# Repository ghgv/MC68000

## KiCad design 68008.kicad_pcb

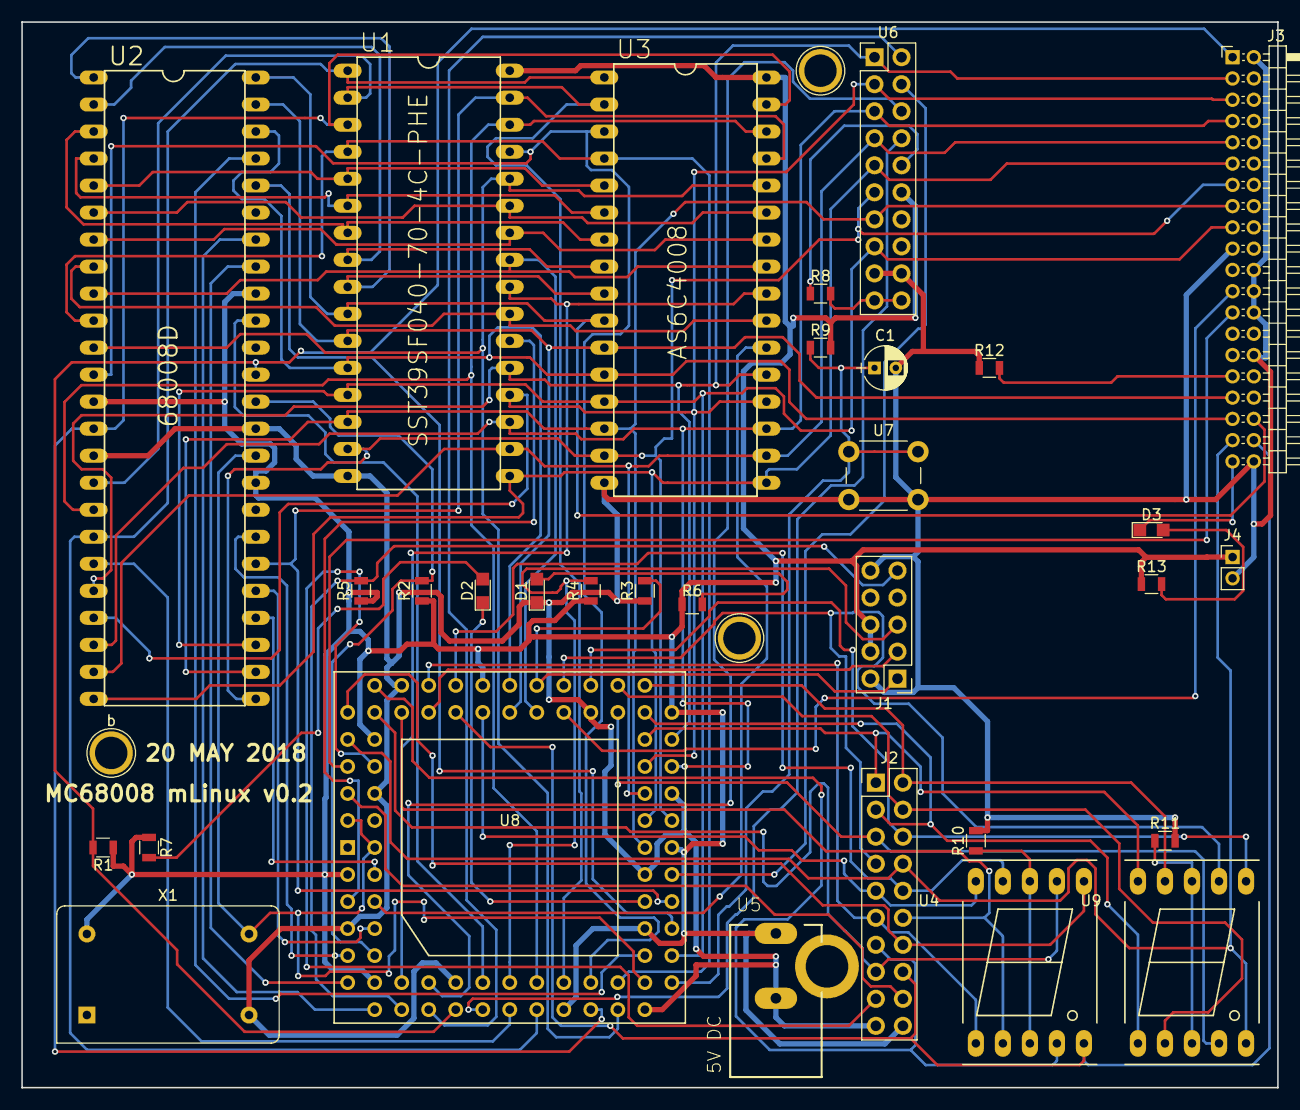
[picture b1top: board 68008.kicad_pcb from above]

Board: 2 copper layers, 118.1 x 100.2 mm, 34 parts (0 on the bottom side), 84 nets.

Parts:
C1: 10uF; CP_Radial_D4.0mm_P2.00mm
D1: Power; LED_0805
D2: status; LED_0805
D3: IDE; LED_0805
J1: CPLD; Pin_Header_Straight_2x05_Pitch2.54mm
J2: PORTS; Pin_Header_Straight_2x10_Pitch2.54mm
J3: Conn_02x20_Odd_Even; Pin_Header_Angled_2x20_Pitch2.00mm
J4: Conn_01x02; Pin_Header_Straight_1x02_Pitch2.00mm
R1, R2, R3, R4, R5: 10K; R_0805
R6, R7, R12, R13: 1K; R_0805
R8: 10KR; R_0805
R9: R; R_0805
R10, R11: 680; R_0805
U1: SST39SF040-70-4C-PHE; DIL32
U2: 68008D; DIL48
U3: AS6C4008; DIL32
U4: Hi; 7SegmentLED_LTS6760_LTS6780
U5: 5V DC; DCJ0202
U6: FT245R; Pin_Header_Straight_2x10_Pitch2.54mm
U7: reset; SW_PUSH_6mm
U8: EPM7486-84; PLCC84
U9: Low; 7SegmentLED_LTS6760_LTS6780
X1: OSCILLATOR; Oscillator_DIP-14
a: 1pin
b: 1pin
c: 1pin

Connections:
/-DASP: D3.1, J3.39
/-IOR: J3.25, U8.79
/-IOW: J3.23, U8.61
/A0: J3.35, U1.12, U2.46, U3.12, U8.64
/A1: J3.33, U1.11, U2.47, U3.11, U8.65
/A2: J3.36, U1.10, U2.48, U3.10
/A3: U1.9, U2.1, U3.9
/A4: U1.8, U2.2, U3.8
/A5: U1.7, U2.3, U3.7
/A6: U1.6, U2.4, U3.6
/A7: U1.5, U2.5, U3.5
/A8: U1.27, U2.6, U3.27
/A9: U1.26, U2.7, U3.26
/A10: U1.23, U2.8, U3.23
/A11: U1.25, U2.9, U3.25, U8.63
/A12: U1.4, U2.10, U3.4, U8.31
/A13: U1.28, U2.11, U3.28, U8.30
/A14: U1.29, U2.12, U3.3, U8.29
/A15: U1.3, U2.14, U3.31, U8.28
/A16: U1.2, U2.16, U3.2, U8.27
/A17: U1.30, U2.17, U3.30, U8.25
/A18: U1.1, U2.18, U3.1, U8.24
/A19: U2.19, U8.22
/AS: U2.28, U8.4
/BTN: C1.1, R9.1, U7.1, U8.33
/CERAM: U1.22, U8.5
/CEROM: U3.22, U8.6
/CLK: U2.34, U8.2, U8.34, U8.83, X1.8
/D0: J3.17, U1.13, U2.27, U3.13, U6.15, U8.35
/D1: J3.15, U1.14, U2.26, U3.14, U6.13, U8.44
/D2: J3.13, U1.15, U2.25, U3.15, U6.11, U8.45
/D3: J3.11, U1.17, U2.24, U3.17, U6.9, U8.46
/D4: J3.9, U1.18, U2.23, U3.18, U6.7, U8.48
/D5: J3.7, U1.19, U2.22, U3.19, U6.5, U8.49
/D6: J3.5, U1.20, U2.21, U3.20, U6.3, U8.50
/D7: J3.3, U1.21, U2.20, U3.21, U6.1, U8.51
/DS: U2.29, U8.8
/DTACK: U2.31, U8.9
/FC0: U2.45, U8.36
/FC1: U2.44, U8.37
/HALT: R2.2, U2.36, U8.10
/INTR1: J2.17, U8.80
/INTR2: J2.18, U8.81
/INTRQ: J3.31, R12.2
/IPL1: U2.41, U8.11
/IPL2: U2.42, U8.12
/OE: U1.24, U3.24, U8.15
/PA0: J2.1, U8.52, U9.10
/PA1: J2.2, U8.54, U9.9
/PA2: J2.3, U8.55, U9.1
/PA3: J2.4, U8.56, U9.2
/PA4: J2.5, U8.57, U9.4
/PA5: J2.6, U8.58, U9.6
/PA6: J2.7, U8.60, U9.7
/PB0: J2.9, U4.10, U8.67
/PB1: J2.10, U4.9, U8.68
/PB2: J2.11, U4.1, U8.70
/PB3: J2.12, U4.2, U8.73
/PB4: J2.13, U4.4, U8.74
/PB5: J2.14, U4.6, U8.75
/PB6: J2.15, U4.7, U8.76
/RD: U6.2, U8.16
/RESET: J3.1, R1.2, U2.37, U8.18
/RW: U1.31, U2.30, U3.29, U8.39
/RXF: U6.6, U8.17
/STATUS: D2.1, U8.40
/TCK: J1.1, R3.2, U8.62
/TDI: J1.9, R5.2, U8.14
/TDO: J1.3, U8.71
/TMS: J1.5, R4.2, U8.23
/TXE: U6.8, U8.20
/VCCIO: R8.2, U6.19, U6.20
/VPA: U2.39, U8.21
/WR: U6.4, U8.41
/_CS0: J2.8, J3.37, U8.77, U9.5
/_CS1: J2.16, J3.38, U4.5, U8.69
GND: C1.2, D1.1, J1.2, J1.10, J2.19, J3.2, J3.19, J3.22, J3.24, J3.26, J3.30, J3.40, J4.2, R3.1, R10.2, R11.2, R12.1, U1.16, U2.15, U2.35, U3.16, U5.3, U6.17, U6.18, U7.2, U8.7, U8.19, U8.32, U8.42, U8.47, U8.59, U8.72, U8.82, X1.7
unnamed: D1.2, R6.2
unnamed: D2.2, R7.2
unnamed: D3.2, R13.2
unnamed: R8.1, U6.10
unnamed: R10.1, U4.3, U4.8
unnamed: R11.1, U9.3, U9.8
VCC: J1.4, J1.6, J2.20, J4.1, R1.1, R2.1, R4.1, R5.1, R6.1, R7.1, R9.2, R13.1, U1.32, U2.13, U2.33, U2.40, U3.32, U5.1, U6.12, U8.3, U8.13, U8.26, U8.38, U8.43, U8.53, U8.66, U8.78, X1.14

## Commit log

2019-11-14 Second MC68000 project
